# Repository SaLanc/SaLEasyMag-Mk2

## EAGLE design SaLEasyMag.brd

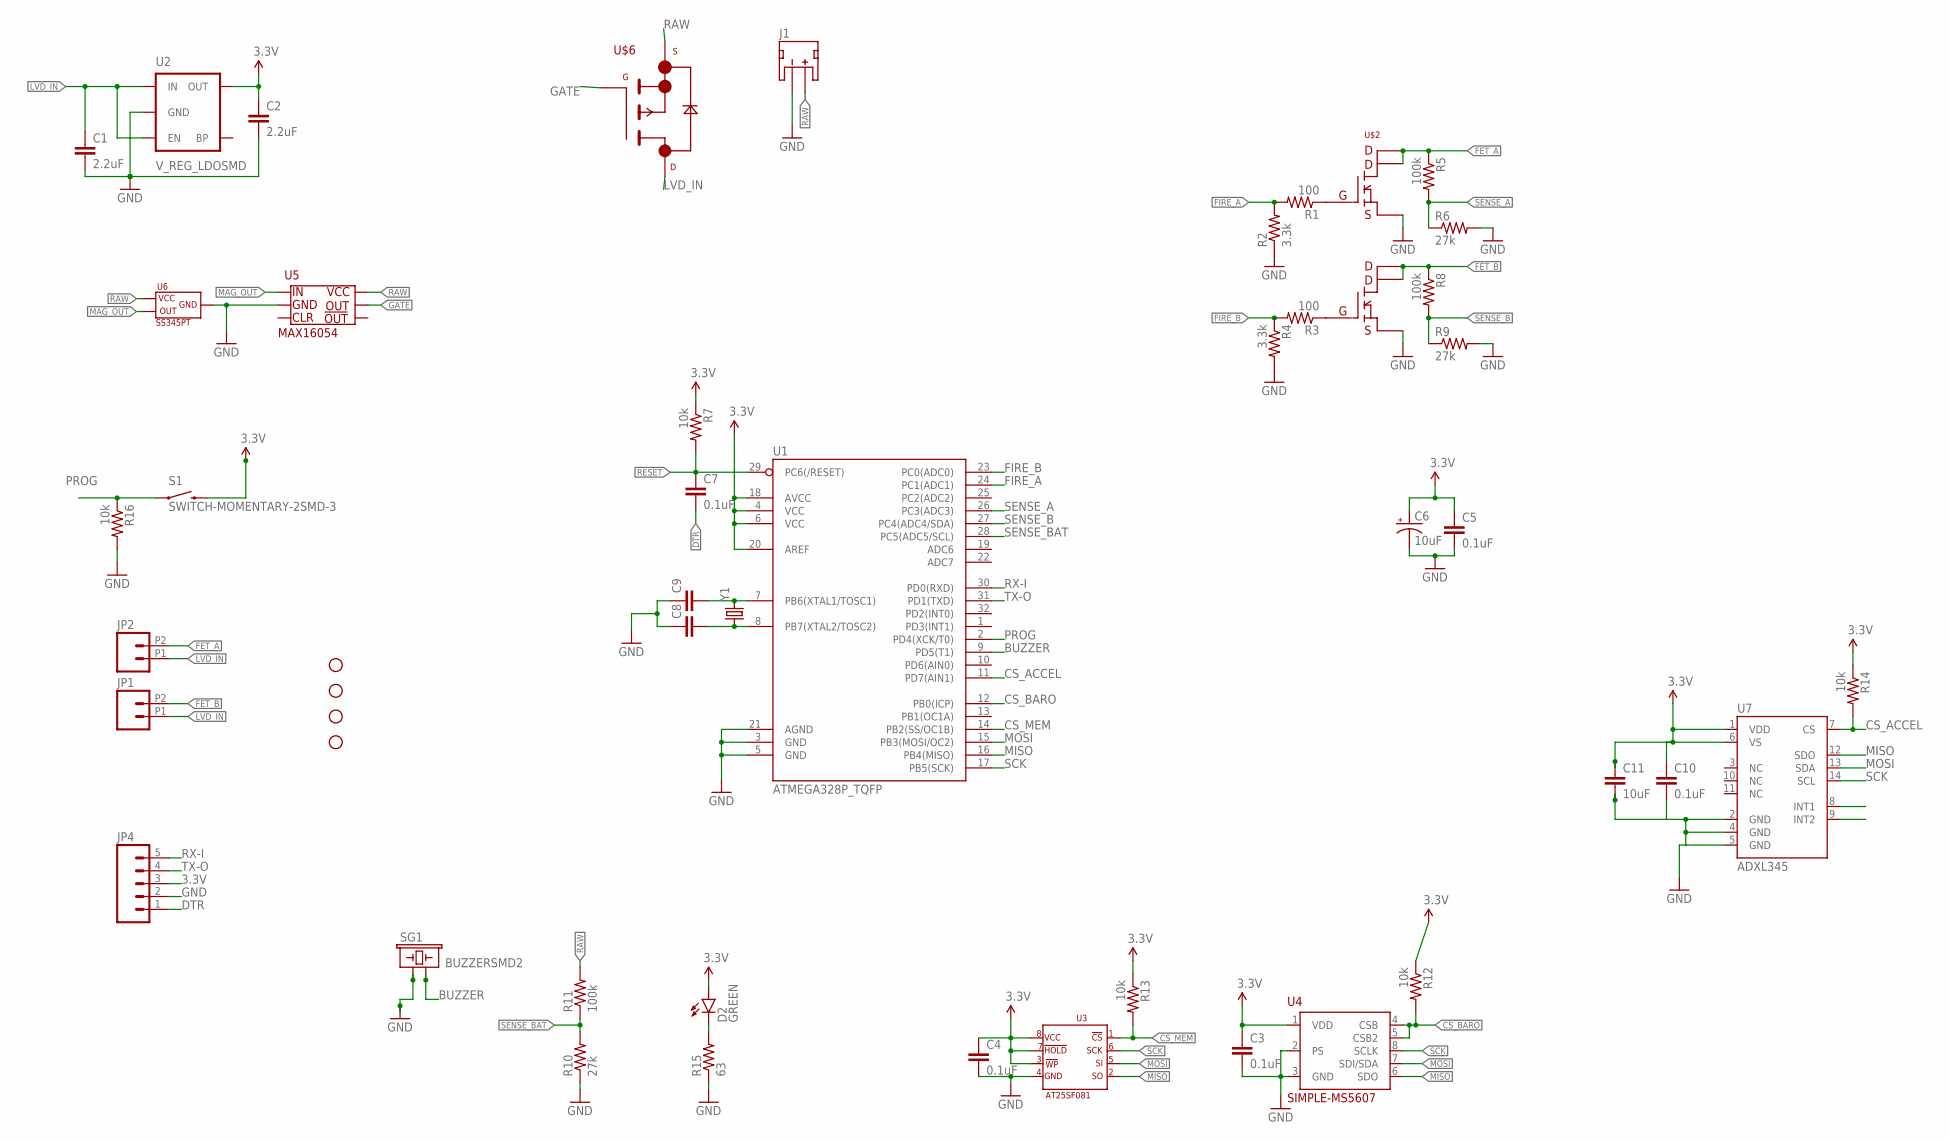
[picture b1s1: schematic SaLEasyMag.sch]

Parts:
C1, C2: 2.2uF; 0603-CAP
C3, C4, C5, C7, C10: 0.1uF; 0603-CAP
C6: 10uF; EIA3216
C8, C9: CAP0402-CAP; 0402-CAP
C11: 10uF; 0603-CAP
D2: GREEN; LED-1206
J1: JST_2MM_MALE; JST-2-SMD
JP1, JP2: M022.54MM_SCREWTERM; 1X02_2.54_SCREWTERM
JP4: M05SMD; 1X05-1MM
R1, R3: 100; 0603-RES
R2, R4: 3.3k; 0603-RES
R5, R8, R11: 100k; 0603-RES
R6, R9, R10: 27k; 0603-RES
R7, R12, R13, R14, R16: 10k; 0603-RES
R15: 63; 0603-RES
S1: SWITCH-MOMENTARY-2SMD-3; TACTILE_SWITCH_SMD-3
SG1: BUZZERSMD2; BUZZER-CCV
STANDOFF1, STANDOFF2, STANDOFF3, STANDOFF4: STAND-OFF
U1: ATMEGA328P_TQFP; TQFP32-08
U2: V_REG_LDOSMD; SOT23-5
U3: AT25SF081
U4: SIMPLE-MS5607; MS5607
U5: MAX16054
U6: SS345PT
U7: ADXL345; LGA14
U$2: SI7232DN
U$6: SI7615ADN
Y1: CRYSTAL5X3; CRYSTAL-SMD-5X3

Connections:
3.3V: C2.1, C3.1, C4.1, C5.1, C6.A (+), C10.1, C11.1, D2.A, JP4.3, R7.1, R12.1, R13.1, R14.1, S1.4 (2), U1.4 (VCC), U1.6 (VCC), U1.18 (AVCC), U1.20 (AREF), U2.5 (OUT), U3.!HOLD, U3.!WP, U3.VCC, U4.1 (VDD), U7.1 (VDD), U7.6 (VS)
BUZZER: SG1.- (2), U1.9 (PD5(T1))
CS_ACCEL: R14.2, U1.11 (PD7(AIN1)), U7.7 (CS)
CS_BARO: R12.2, U1.12 (PB0(ICP)), U4.4 (CSB), U4.5 (CSB2)
CS_MEM: R13.2, U1.14 (PB2(SS/OC1B)), U3.!CS
DTR: C7.2, JP4.1
FET_A: JP2.P2 (2), R5.1, U$2.7 (PIN7), U$2.8 (PIN8)
FET_B: JP1.P2 (2), R8.1, U$2.5 (PIN5), U$2.6 (PIN6)
FIRE_A: R1.2, R2.2, U1.24 (PC1(ADC1))
FIRE_B: R3.2, R4.1, U1.23 (PC0(ADC0))
GATE: U5.OUT, U$6.G
GND: C1.2, C2.2, C3.2, C4.2, C5.2, C6.C (-), C8.1, C9.1, C10.2, C11.2, J1.1 (-), JP4.2, R2.1, R4.2, R6.2, R9.2, R10.1, R15.1, R16.2, SG1.+ (1), U1.3 (GND), U1.5 (GND), U1.21 (AGND), U2.2 (GND), U3.GND, U4.2 (PS), U4.3 (GND), U5.GND, U6.GND, U7.2 (GND), U7.4 (GND), U7.5 (GND), U$2.1 (PIN1), U$2.3 (PIN3)
LVD_IN: C1.1, JP1.P1 (1), JP2.P1 (1), U2.1 (IN), U2.3 (EN), U$6.D1 (D), U$6.D2 (D), U$6.D3 (D), U$6.D4 (D)
MAG_OUT: U5.IN, U6.OUT
MISO: U1.16 (PB4(MISO)), U3.SO, U4.6 (SDO), U7.12 (SDO)
MOSI: U1.15 (PB3(MOSI/OC2)), U3.SI, U4.7 (SDI/SDA), U7.13 (SDA)
unnamed: D2.C, R15.2
unnamed: R3.1, U$2.4 (PIN4)
unnamed: C9.2, U1.7 (PB6(XTAL1/TOSC1)), Y1.3 (2)
unnamed: C8.2, U1.8 (PB7(XTAL2/TOSC2)), Y1.1
unnamed: R1.1, U$2.2 (PIN2)
PROG: R16.1, S1.1, U1.2 (PD4(XCK/T0))
RAW: J1.2 (+), R11.2, U5.VCC, U6.VCC, U$6.S1 (S), U$6.S2 (S), U$6.S3 (S)
RESET: C7.1, R7.2, U1.29 (PC6(/RESET))
RX-I: JP4.5, U1.30 (PD0(RXD))
SCK: U1.17 (PB5(SCK)), U3.SCK, U4.8 (SCLK), U7.14 (SCL)
SENSE_A: R5.2, R6.1, U1.26 (PC3(ADC3))
SENSE_B: R8.2, R9.1, U1.27 (PC4(ADC4/SDA))
SENSE_BAT: R10.2, R11.1, U1.28 (PC5(ADC5/SCL))
TX-O: JP4.4, U1.31 (PD1(TXD))

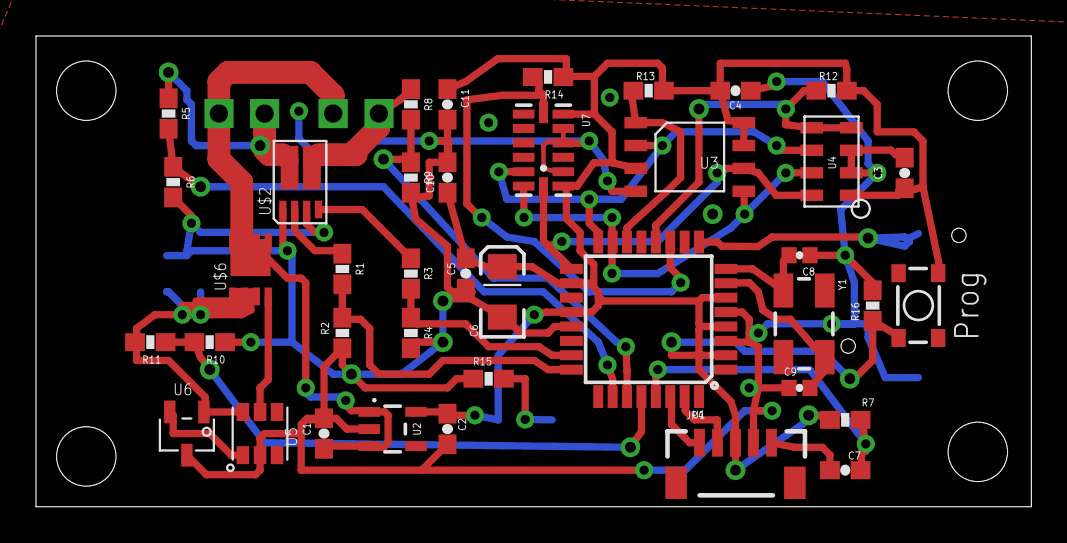
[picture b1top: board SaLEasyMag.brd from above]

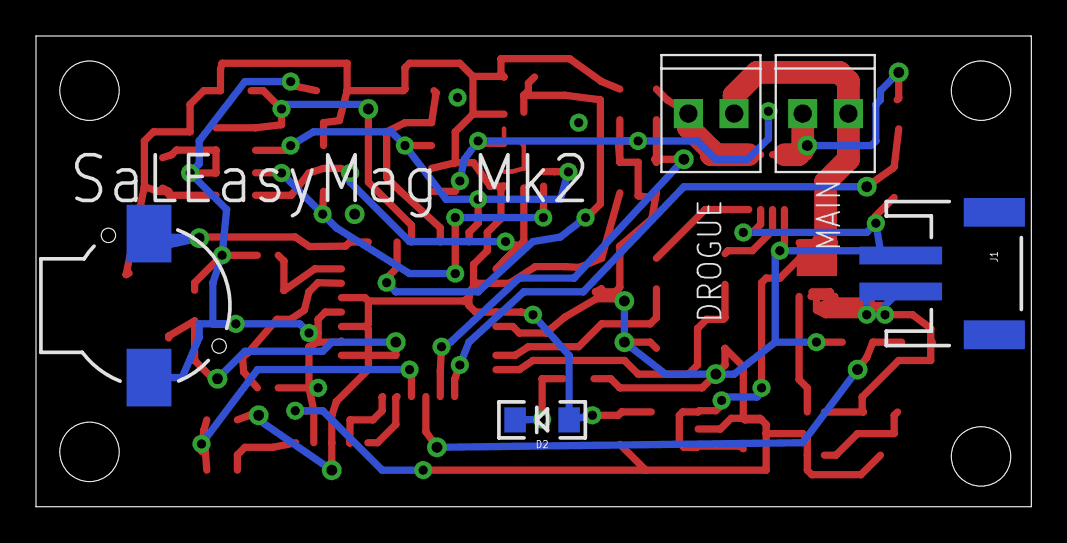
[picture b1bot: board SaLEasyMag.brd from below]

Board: 2 copper layers, 55.3 x 26.2 mm, 48 parts (5 on the bottom side), 30 nets.

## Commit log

2015-12-24 :neckbeard: Added .gitattributes & .gitignore files
2015-12-24 initial

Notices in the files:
parts and their libraries:
SparkFun-Passives: Licensing: Creative Commons ShareAlike 4.0 International - https://creativecommons.org/licenses/by-sa/4.0
